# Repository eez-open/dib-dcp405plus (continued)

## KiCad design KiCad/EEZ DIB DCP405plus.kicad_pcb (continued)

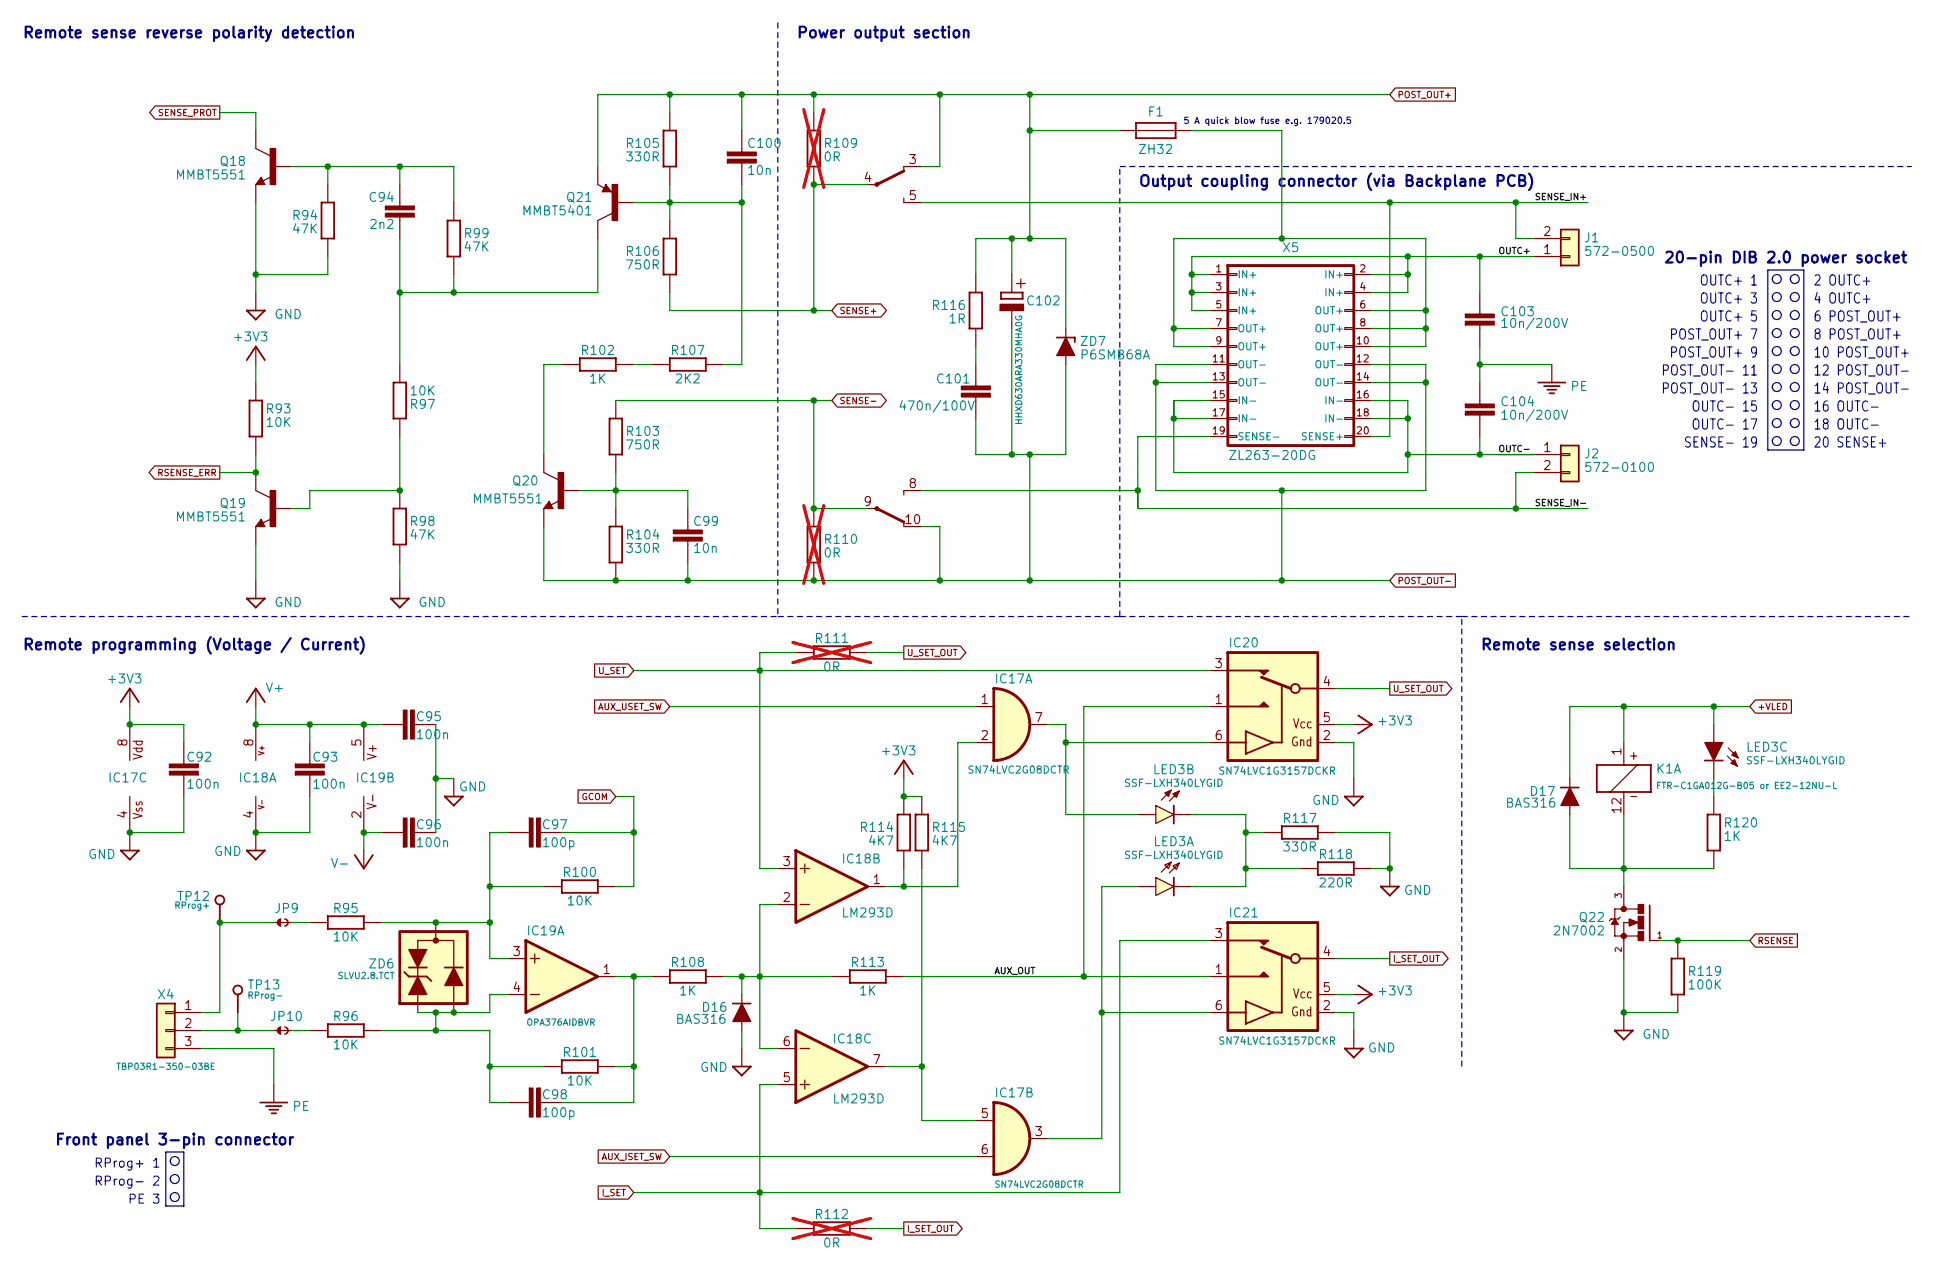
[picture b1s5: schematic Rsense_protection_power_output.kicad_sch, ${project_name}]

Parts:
C92, C93, C95, C96: 100n; C_0603_1608Metric; DigiKey 1276-6717-1-ND
C94: 2n2; C_0805_2012Metric; DigiKey 1276-2478-1-ND
C97, C98: 100p; C_0805_2012Metric; DigiKey 399-15000-1-ND
C99, C100: 10n; C_0805_2012Metric; DigiKey 490-7194-1-ND
C101: 470n/100V; C_0805_2012Metric; DigiKey 587-5014-1-ND
C102: HHXD630ARA330MHA0G; CAPAE830X1050N; DigiKey 565-HHXD630ARA330MHA0GCT-ND
C103, C104: 10n/200V; C_1206_3216Metric; DigiKey 311-4491-1-ND
D16, D17: BAS316; SOD-323_1P8X1P35_ONS-M; DigiKey 5399-BAS316CT-ND
F1: ZH32; DigiKey 732-11370-ND
IC17: SN74LVC2G08DCTR; DCT8; DigiKey 1727-5987-1-ND
IC18: LM293D; SOIC127P600X173-8N; DigiKey LM293DR2GOSCT-ND
IC19: OPA376AIDBVR; SOT23-5L_STM; DigiKey 296-39130-1-ND
IC20, IC21: SN74LVC1G3157DCKR; SOT65P210X110-6N; DigiKey 296-14909-1-ND
J1: 572-0500; Mouser 164-6221
J2: 572-0100; Mouser 164-6220
JP9, JP10: JP2-NOCUT-0805; JP2 shorted (0603)
K1: FTR-C1GA012G-B05 or EE2-12NU-L; FTR-C1; DigiKey 399-10997-1-ND
LED3: SSF-LXH340LYGID; DigiKey SSF-LXH340LYGID-ND
Q18, Q19, Q20: MMBT5551; SOT23-BEC; DigiKey MMBT5551LT1GOSCT-ND
Q21: MMBT5401; SOT23-BEC; DigiKey MMBT5401-FDICT-ND
Q22: 2N7002; SOT103P240X110-3N; DigiKey T2N7002AKLMCT-ND
R93, R95, R96, R97, R100, R101: 10K; R_0805_2012Metric; DigiKey 311-10.0KCRCT-ND
R94, R98, R99: 47K; R_0805_2012Metric; DigiKey RHM47KKCT-ND
R102, R108, R113, R120: 1K; R_0805_2012Metric; DigiKey 311-1.00KCRCT-ND
R103, R106: 750R; R_0805_2012Metric; DigiKey A126385CT-ND
R104, R105, R117: 330R; R_0805_2012Metric; DigiKey A129743CT-ND
R107: 2K2; R_0805_2012Metric; DigiKey 311-2.20KCRCT-ND
R109, R110, R111, R112: 0R; R_0603_1608Metric; not fitted
R114, R115: 4K7; R_0805_2012Metric; DigiKey 311-4.70KCRCT-ND
R116: 1R; R_0805_2012Metric; DigiKey 13-RC0805FR-131RLCT-ND
R118: 220R; R_0805_2012Metric; DigiKey RMCF0805FT220RCT-ND
R119: 100K; R_0805_2012Metric; DigiKey RMCF0805FT100KCT-ND
TP12, TP13: PCB_TEST_TABSHIELD; Testhole 24_50mils
X4: TBP03R1-350-03BE; DigiKey 2223-TBP03R1-350-03BE-ND
X5: ZL263-20DG; SSW-110-02-T-D-RA; DigiKey PPPC102LJBN-RC
ZD6: SLVU2.8.TCT; SOT23-3; DigiKey SLVU2.8.TCTCT-ND
ZD7: P6SMB68A; DO214AA; DigiKey P6SMB68ABBCT-ND

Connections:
+3V3: C92.2, IC17.8 (VDD), IC20.5 (VDD), IC21.5 (VDD), R93.2, R114.1, R115.1; also elsewhere on the board
+VLED: D17.C, K1.1 (C1), LED3.YA; also elsewhere on the board
/Rsense protection, power output, Rprog/AUX_OUT: IC20.1 (NO), IC21.1 (NO), R113.1
/Rsense protection, power output, Rprog/OUTC+: C103.1, J1.1, X5.1 (IN+), X5.2 (IN+), X5.3 (IN+), X5.4 (IN+), X5.5 (IN+)
/Rsense protection, power output, Rprog/OUTC-: C104.2, J2.1, X5.15 (IN-), X5.16 (IN-), X5.17 (IN-), X5.18 (IN-)
/Rsense protection, power output, Rprog/SENSE_IN+: J1.2, K1.5 (NO), X5.20 (SENSE+)
/Rsense protection, power output, Rprog/SENSE_IN-: J2.2, K1.8 (NO), X5.19 (SENSE-)
AUX_ISET_SW: IC17.6 (I1); also elsewhere on the board
AUX_USET_SW: IC17.1 (I0); also elsewhere on the board
GCOM: C97.1, R100.1; also elsewhere on the board
GND: C92.1, C93.2, C95.2, C96.2, D16.A, IC17.4 (VSS), IC18.4 (V-), IC20.2 (GND), IC21.2 (GND), Q18.E, Q19.E, Q22.2 (S), R94.1, R98.1, R117.1, R118.1, R119.1; also elsewhere on the board
I_SET: IC18.5 (+IN), IC21.3 (NC), R112.2; also elsewhere on the board
I_SET_OUT: IC21.4 (COM), R112.1; also elsewhere on the board
unnamed: C94.1, Q18.B, R94.2, R99.2
unnamed: C94.2, Q21.C, R97.2, R99.1
unnamed: C99.1, Q20.B, R103.1, R104.2
unnamed: C100.2, Q21.B, R105.1, R106.2, R107.2
unnamed: C101.2, R116.2
unnamed: F1.2, X5.6 (OUT+), X5.7 (OUT+), X5.8 (OUT+), X5.9 (OUT+), X5.10 (OUT+)
unnamed: IC17.2 (I1), IC18.1 (OUT), R114.2
unnamed: IC17.7 (O), IC20.6 (CTRL), LED3.GA
unnamed: IC17.5 (I0), IC18.7 (OUT), R115.2
unnamed: IC17.3 (O), IC21.6 (CTRL), LED3.RA
unnamed: D16.C, IC18.2 (-IN), IC18.6 (-IN), R108.1, R113.2
unnamed: C97.2, IC19.3 (+IN), R95.1, R100.2, ZD6.3
unnamed: C98.2, IC19.4 (-IN), R96.1, R101.2, ZD6.1, ZD6.2
unnamed: C98.1, IC19.1 (OUT), R101.1, R108.2
unnamed: JP9.2, R95.2
unnamed: JP10.2, R96.2
unnamed: D17.A, K1.12 (C2), Q22.3 (D), R120.1
unnamed: LED3.GC, LED3.RC, R117.2, R118.2
unnamed: LED3.YC, R120.2
unnamed: Q19.B, R97.1, R98.2
unnamed: Q20.C, R102.1
unnamed: R102.2, R107.1
unnamed: JP9.1, TP12.1 (P$1_1), X4.1
unnamed: JP10.1, TP13.1 (P$1_1), X4.2
PE: C103.2, C104.1, X4.3; also elsewhere on the board
POST_OUT+: C100.1, C102.+, F1.1, K1.3 (NC), Q21.E, R105.2, R109.1, R116.1, ZD7.C; also elsewhere on the board
POST_OUT-: C99.2, C101.1, C102.-, K1.10 (NC), Q20.E, R104.1, R110.2, X5.11 (OUT-), X5.12 (OUT-), X5.13 (OUT-), X5.14 (OUT-), ZD7.A; also elsewhere on the board
RSENSE: Q22.1 (G), R119.2; also elsewhere on the board
RSENSE_ERR: Q19.C, R93.1; also elsewhere on the board
SENSE+: K1.4 (COM), R106.1, R109.2; also elsewhere on the board
SENSE-: K1.9 (COM), R103.2, R110.1; also elsewhere on the board
SENSE_PROT: Q18.C; also elsewhere on the board
U_SET: IC18.3 (+IN), IC20.3 (NC), R111.2; also elsewhere on the board
U_SET_OUT: IC20.4 (COM), R111.1; also elsewhere on the board
V+: C93.1, C95.1, IC18.8 (V+), IC19.5 (V+); also elsewhere on the board
V-: C96.1, IC19.2 (V-); also elsewhere on the board

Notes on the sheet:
8 POST_OUT+
PE 3
16 OUTC-
POST_OUT- 11
12 POST_OUT-
Remote sense reverse polarity detection
POST_OUT+ 9
OUTC- 17
Output coupling connector (via Backplane PCB)
POST_OUT- 13
Remote programming (Voltage / Current)
10 POST_OUT+
4 OUTC+
6 POST_OUT+
2 OUTC+
OUTC+ 5
14 POST_OUT-
18 OUTC-
POST_OUT+ 7
OUTC+ 1
RProg+ 1
20 SENSE+
Front panel 3-pin connector
OUTC+ 3
5 A quick blow fuse e.g. 179020.5
RProg- 2
Power output section
Remote sense selection
SENSE- 19
OUTC- 15
20-pin DIB 2.0 power socket

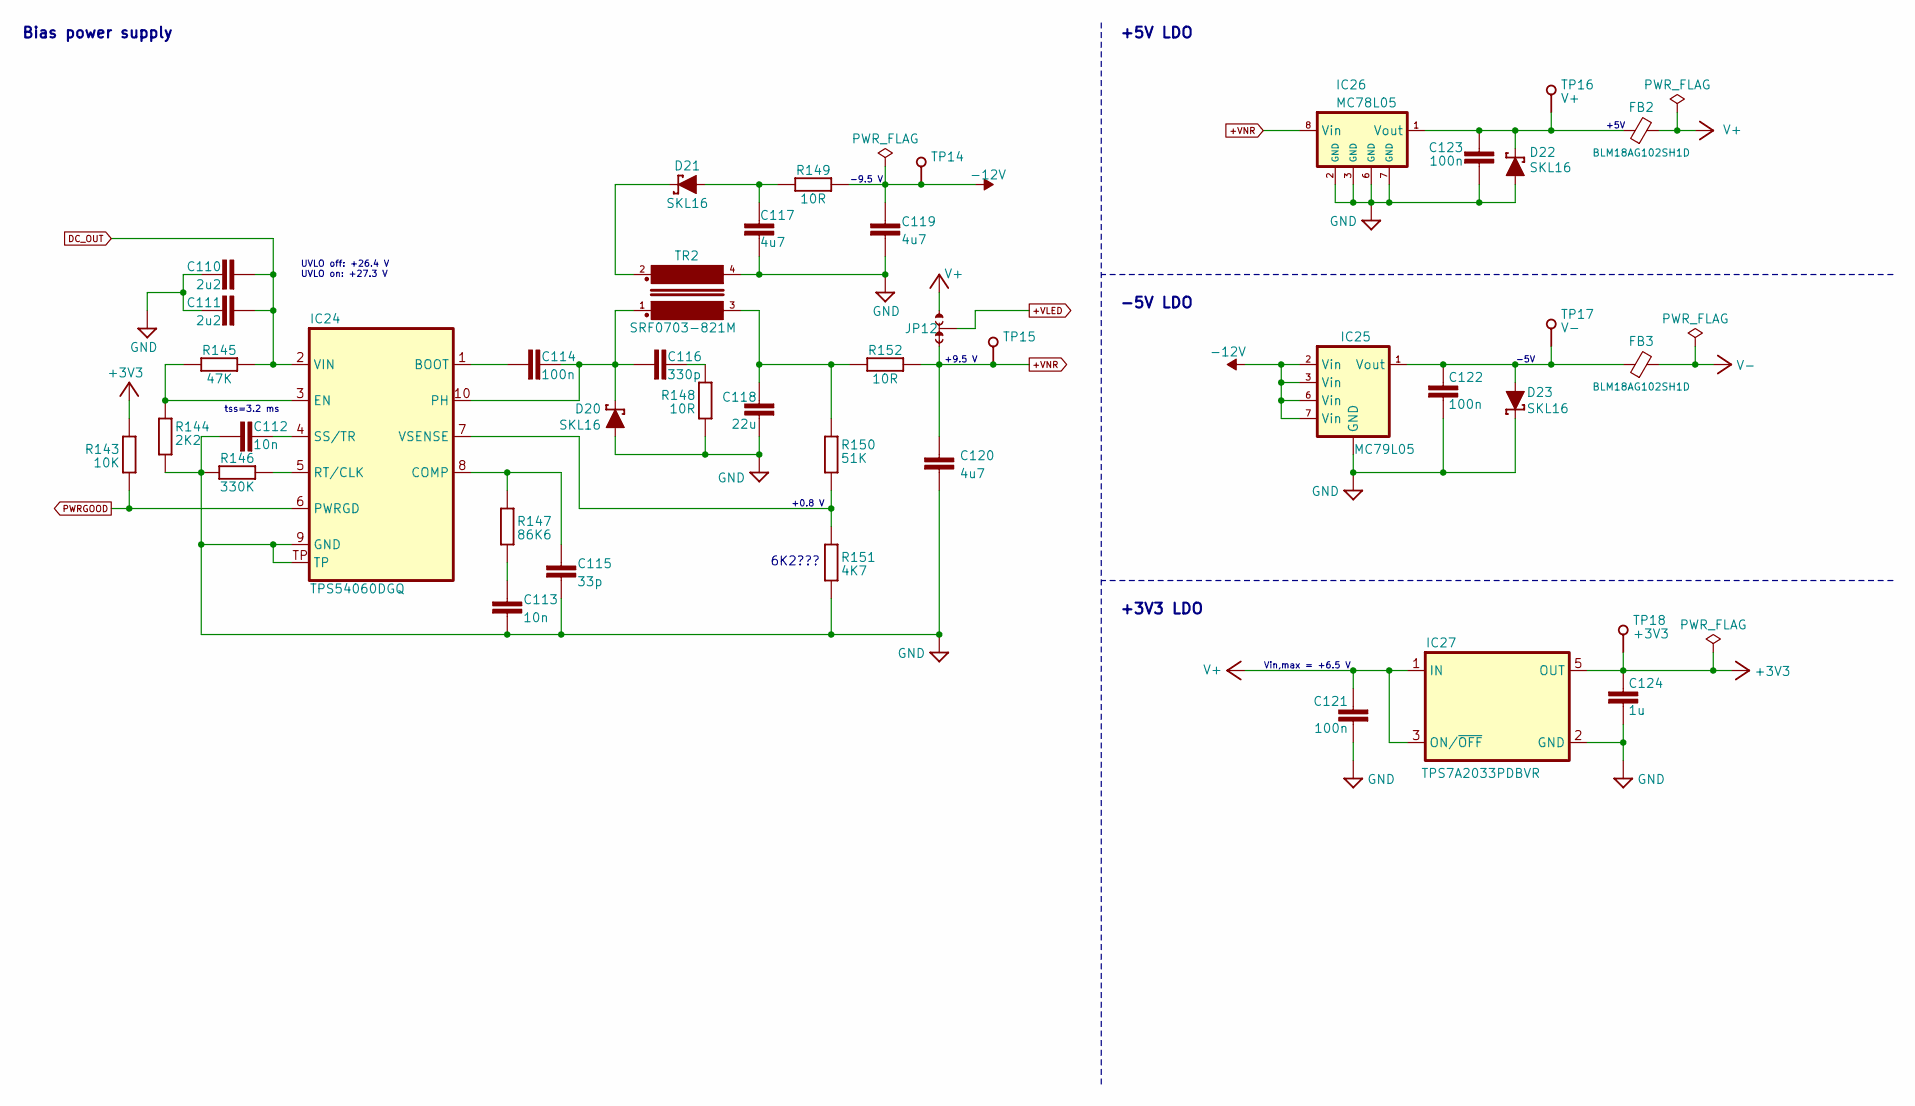
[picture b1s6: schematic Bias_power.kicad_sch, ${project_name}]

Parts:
C110, C111: 2u2; C_1206_3216Metric; DigiKey 1276-3138-1-ND
C112, C113: 10n; C_0805_2012Metric; DigiKey 490-7194-1-ND
C114, C121, C122, C123: 100n; C_0603_1608Metric; DigiKey 1276-6717-1-ND
C115: 33p; C_0805_2012Metric; DigiKey 399-C0805C330J5GACTUCT-ND
C116: 330p; C_0805_2012Metric; DigiKey 311-1117-1-ND
C117, C119, C120: 4u7; C_0805_2012Metric; DigiKey 1276-CL21A475KACLRNCCT-ND
C118: 22u; C_1210_3225Metric; DigiKey 1276-1851-1-ND
C124: 1u; C_0805_2012Metric; DigiKey 1276-2931-1-ND
D20, D21, D22, D23: SKL16; SOD123; DigiKey RB160MM-60CT-ND
FB2, FB3: BLM18AG102SH1D; BEAD0603; DigiKey 490-7809-1-ND
IC24: TPS54060DGQ; SOP50P490X110-11N; DigiKey 296-37148-1-ND
IC25: MC79L05; SOIC127P600X173-8N; DigiKey MC79L05ACDR2GOSCT-ND
IC26: MC78L05; SOIC127P600X173-8N; DigiKey MC78L05ACDR2GOSCT-ND
IC27: TPS7A2033PDBVR; SOT23-5L_STM; DigiKey 296-TPS7A2033PDBVRCT-ND
JP12: JP3 shorted (0603)
R143: 10K; R_0805_2012Metric; DigiKey 311-10.0KCRCT-ND
R144: 2K2; R_0805_2012Metric; DigiKey 311-2.20KCRCT-ND
R145: 47K; R_0805_2012Metric; DigiKey RHM47KKCT-ND
R146: 330K; R_0805_2012Metric; DigiKey A126361CT-ND
R147: 86K6; R_0805_2012Metric; DigiKey 311-86.6KCRCT-ND
R148, R149, R152: 10R; R_0805_2012Metric; DigiKey 311-10.0CRCT-ND
R150: 51K; R_0805_2012Metric; DigiKey 311-51.0KCRCT-ND
R151: 4K7; R_0805_2012Metric; DigiKey 311-4.70KCRCT-ND
TP14, TP15, TP16, TP17, TP18: TEST-PIN_0.9MM; Testhole 24_50mils
TR2: SRF0703-821M; SRF0703; DigiKey SRF0703-821MCT-ND

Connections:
+3V3: C124.2, IC27.5 (OUT), R143.1, TP18.1 (P$1_1); also elsewhere on the board
+VLED: JP12.COM; also elsewhere on the board
+VNR: C120.1, IC26.8 (Vin), JP12.NC, R152.2, TP15.1 (P$1_1); also elsewhere on the board
-12V: C119.1, IC25.2 (Vin), IC25.3 (Vin), IC25.6 (Vin), IC25.7 (Vin), R149.2, TP14.1 (P$1_1); also elsewhere on the board
DC_OUT: C110.1, C111.1, IC24.2 (VIN), R145.2; also elsewhere on the board
GND: C110.2, C111.2, C112.2, C113.1, C115.1, C117.2, C118.2, C119.2, C120.2, C121.1, C122.1, C123.2, C124.1, D20.A, D22.A, D23.C, IC24.9 (GND), IC24.TP, IC25.5 (GND), IC26.2 (GND), IC26.3 (GND), IC26.6 (GND), IC26.7 (GND), IC27.2 (GND), R144.1, R146.1, R148.2, R151.2, TR2.4; also elsewhere on the board
unnamed: C113.2, R147.1
unnamed: C116.2, R148.1
unnamed: C117.1, D21.A, R149.1
unnamed: C118.1, R150.1, R152.1, TR2.3
unnamed: D21.C, TR2.2
unnamed: C114.2, IC24.1 (BOOT)
unnamed: C115.2, IC24.8 (COMP), R147.2
unnamed: IC24.3 (EN), R144.2, R145.1
unnamed: C114.1, C116.1, D20.C, IC24.10 (PH), TR2.1
unnamed: IC24.5 (RT/CLK), R146.2
unnamed: C112.1, IC24.4 (SS/TR)
unnamed: IC24.7 (VSENSE), R150.2, R151.1
unnamed: C122.2, D23.A, FB3.1, IC25.1 (Vout), TP17.1 (P$1_1)
unnamed: C123.1, D22.C, FB2.1, IC26.1 (Vout), TP16.1 (P$1_1)
PWRGOOD: IC24.6 (PWRGD), R143.2; also elsewhere on the board
V+: C121.2, FB2.2, IC27.1 (IN), IC27.3 (ON/~OFF), JP12.NO; also elsewhere on the board
V-: FB3.2; also elsewhere on the board

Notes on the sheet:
+5V
UVLO off: +26.4 V UVLO on: +27.3 V
Vin,max = +6.5 V
+5V LDO
Bias power supply
-5V LDO
+0.8 V
+3V3 LDO
6K2???
-5V
-9.5 V
tss=3.2 ms
+9.5 V

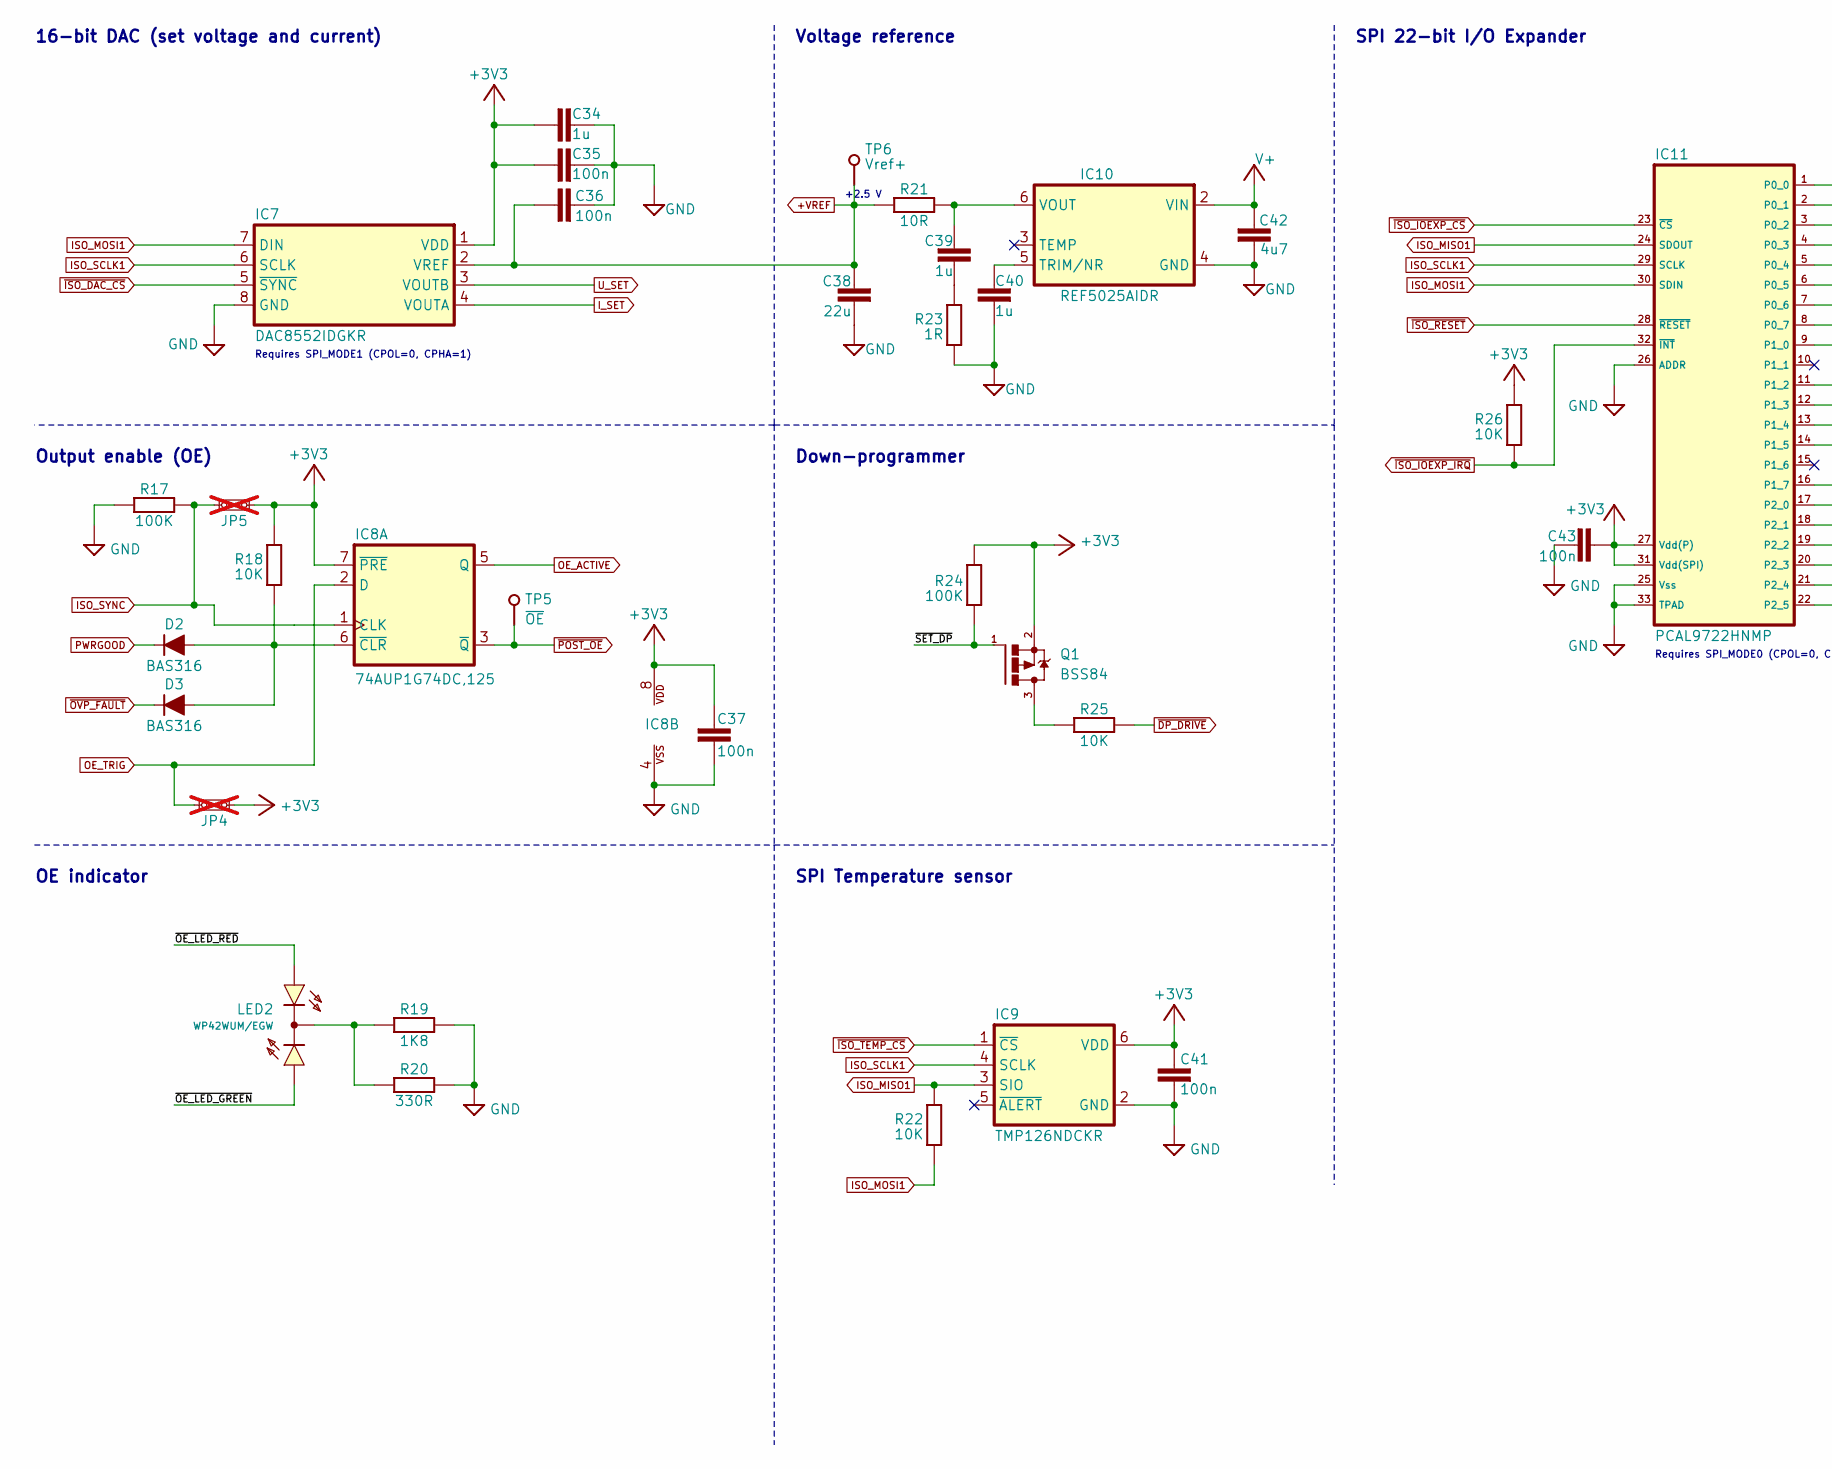
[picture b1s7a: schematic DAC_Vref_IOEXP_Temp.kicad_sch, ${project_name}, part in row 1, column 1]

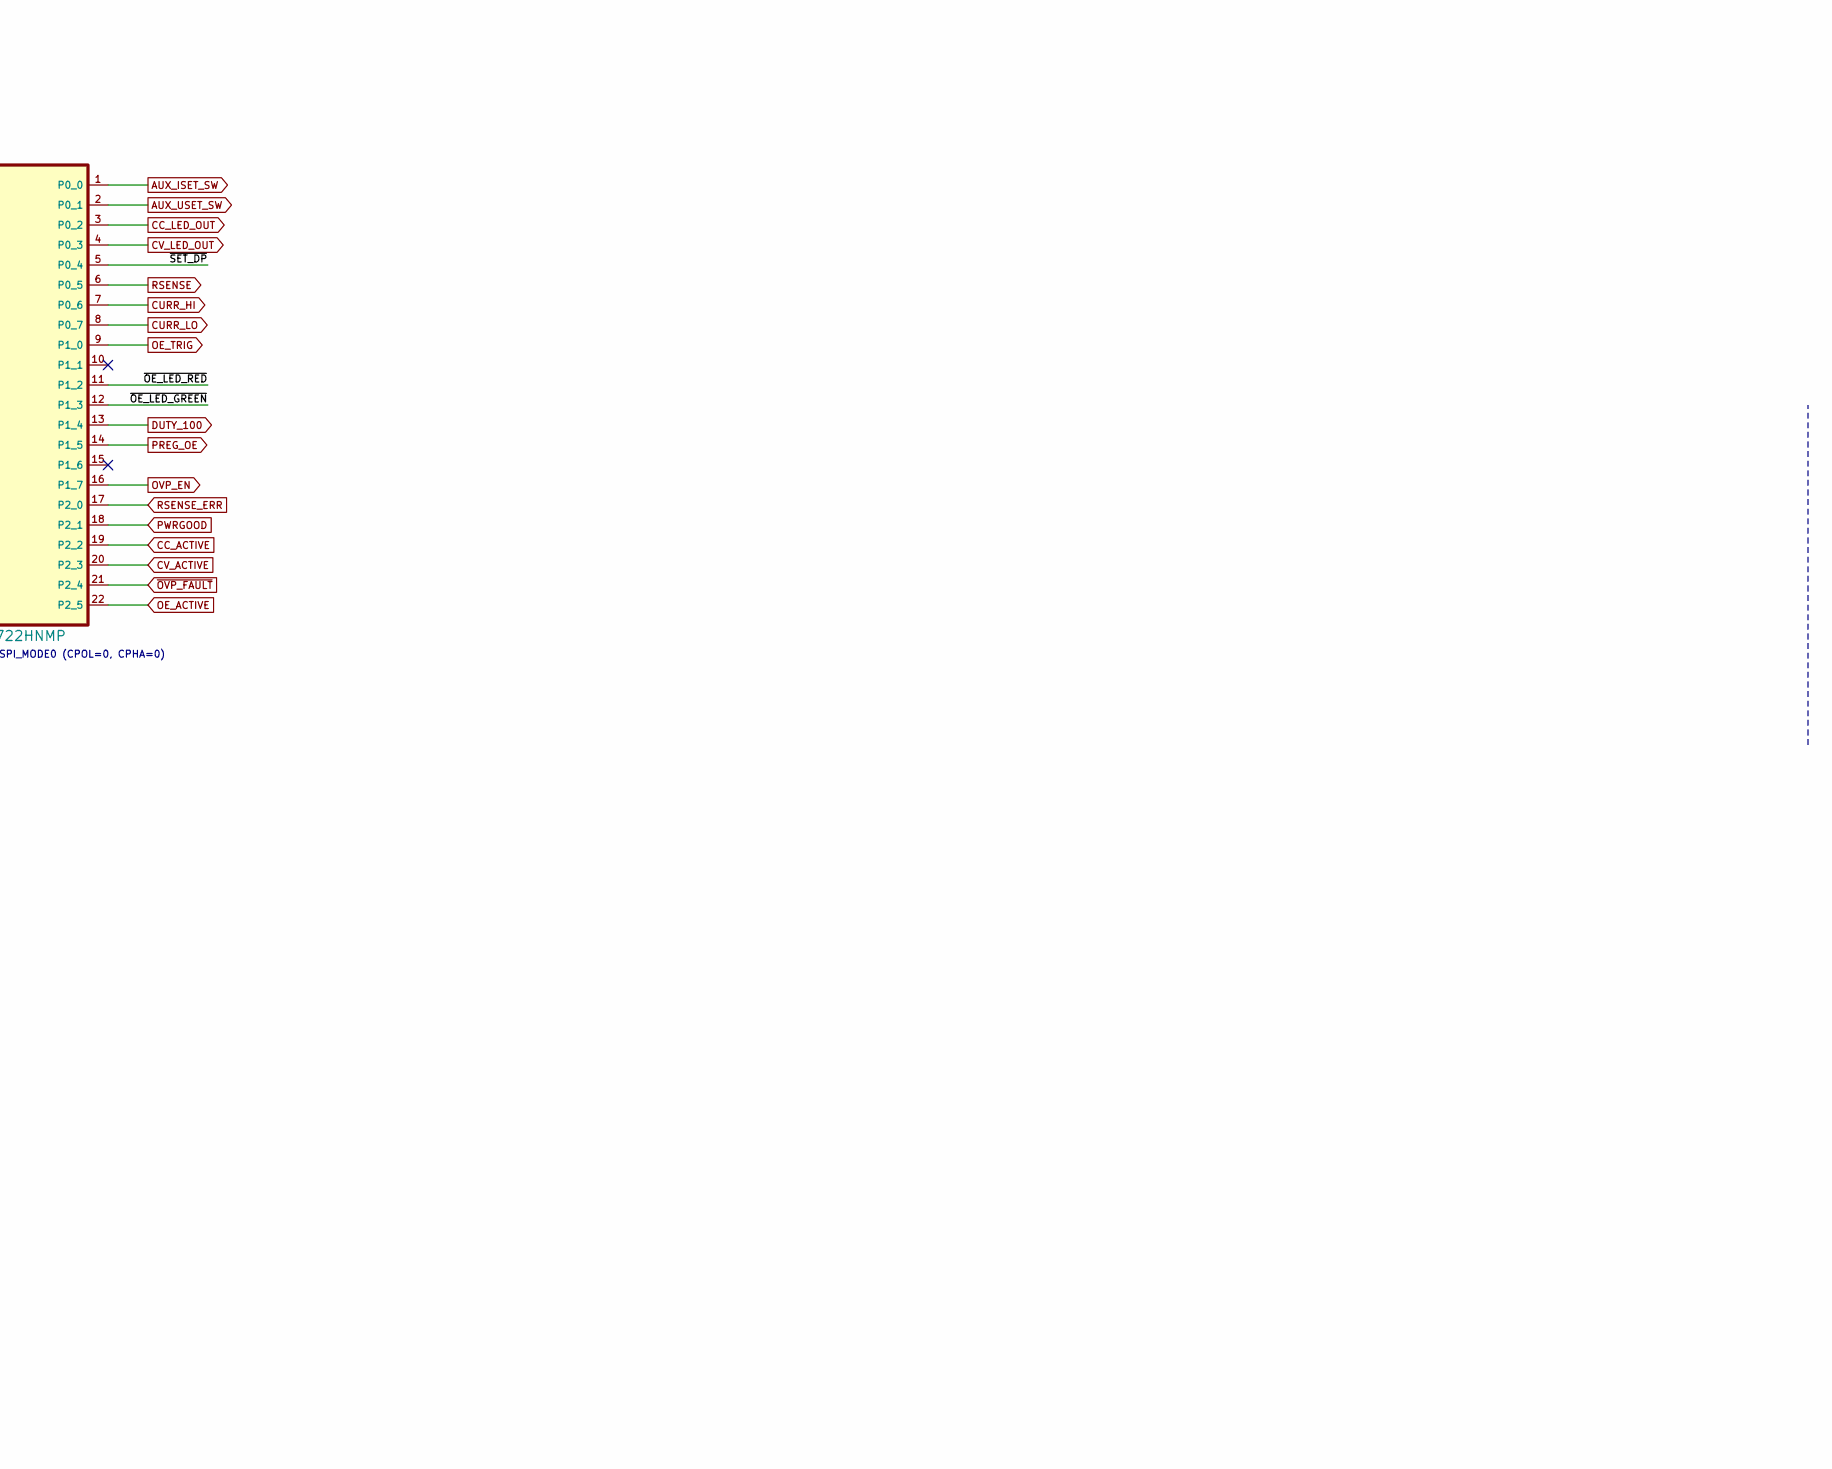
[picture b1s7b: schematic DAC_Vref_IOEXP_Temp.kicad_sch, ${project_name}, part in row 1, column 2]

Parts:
C34, C39, C40: 1u; C_0805_2012Metric; DigiKey 1276-2931-1-ND
C35, C36, C37, C41, C43: 100n; C_0603_1608Metric; DigiKey 1276-6717-1-ND
C38: 22u; C_1210_3225Metric; DigiKey 1276-1851-1-ND
C42: 4u7; C_0805_2012Metric; DigiKey 1276-CL21A475KACLRNCCT-ND
D2, D3: BAS316; SOD-323_1P8X1P35_ONS-M; DigiKey 5399-BAS316CT-ND
IC7: DAC8552IDGKR; DGK8-M; DigiKey 296-46082-1-ND
IC8: 74AUP1G74DC,125; DCU8; DigiKey 1727-74AUP1G74DC-Q100HCT-ND
IC9: TMP126NDCKR; DCK6; DigiKey 296-TMP126NDCKRCT-ND
IC10: REF5025AIDR; SOIC127P600X173-8N; DigiKey 296-41382-1-ND
IC11: PCAL9722HNMP; HVQFN32_SOT617-1_NXP-M; DigiKey 568-PCAL9722HNMPCT-ND
JP4, JP5: M22-2010246; DigiKey M22-2010346-ND; not fitted
LED2: WP42WUM/EGW; L-42WUM-1EGWT; DigiKey 754-1718-ND
Q1: BSS84; SOT103P240X110-3N; DigiKey BSS84LT1GOSCT-ND
R17, R24: 100K; R_0805_2012Metric; DigiKey RMCF0805FT100KCT-ND
R18, R22, R25, R26: 10K; R_0805_2012Metric; DigiKey 311-10.0KCRCT-ND
R19: 1K8; R_0805_2012Metric; DigiKey 311-1.80KCRCT-ND
R20: 330R; R_0805_2012Metric; DigiKey A129743CT-ND
R21: 10R; R_0805_2012Metric; DigiKey 311-10.0CRCT-ND
R23: 1R; R_0805_2012Metric; DigiKey 13-RC0805FR-131RLCT-ND
TP5: TEST-PIN_0.9MM; Testhole 24_50mils
TP6: PCB_TEST_TABSHIELD; Testhole 24_50mils

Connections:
+3V3: C34.1, C35.2, C37.2, C41.1, C43.2, IC7.1 (VDD), IC8.7 (~PRE), IC8.8 (VDD), IC9.6 (VDD), IC11.27 (Vdd(P)), IC11.31 (Vdd(SPI)), JP4.1, JP5.1, Q1.2 (S), R18.2, R24.1, R26.2; also elsewhere on the board
+VREF: C36.2, C38.1, IC7.2 (VREF), R21.1, TP6.1 (P$1_1); also elsewhere on the board
/DAC, OE, Vref, IOEXP, Temp/~OE_LED_GREEN: IC11.12 (P1_3), LED2.GREEN (AG)
/DAC, OE, Vref, IOEXP, Temp/~OE_LED_RED: IC11.11 (P1_2), LED2.RED (AR)
/DAC, OE, Vref, IOEXP, Temp/~SET_DP: IC11.5 (P0_4), Q1.1 (G), R24.2
AUX_ISET_SW: IC11.1 (P0_0); also elsewhere on the board
AUX_USET_SW: IC11.2 (P0_1); also elsewhere on the board
CC_ACTIVE: IC11.19 (P2_2); also elsewhere on the board
CC_LED_OUT: IC11.3 (P0_2); also elsewhere on the board
CURR_HI: IC11.7 (P0_6); also elsewhere on the board
CURR_LO: IC11.8 (P0_7); also elsewhere on the board
CV_ACTIVE: IC11.20 (P2_3); also elsewhere on the board
CV_LED_OUT: IC11.4 (P0_3); also elsewhere on the board
DUTY_100: IC11.13 (P1_4); also elsewhere on the board
GND: C34.2, C35.1, C36.1, C37.1, C38.2, C40.2, C41.2, C42.2, C43.1, IC7.8 (GND), IC8.4 (VSS), IC9.2 (GND), IC10.4 (GND), IC11.25 (Vss), IC11.26 (ADDR), IC11.33 (TPAD), R17.1, R19.2, R20.2, R23.2; also elsewhere on the board
ISO_MISO1: IC9.3 (SIO), IC11.24 (SDOUT), R22.2; also elsewhere on the board
ISO_MOSI1: IC7.7 (DIN), IC11.30 (SDIN), R22.1; also elsewhere on the board
ISO_SCLK1: IC7.6 (SCLK), IC9.4 (SCLK), IC11.29 (SCLK); also elsewhere on the board
ISO_SYNC: IC8.1 (CLK), JP5.2, R17.2; also elsewhere on the board
I_SET: IC7.4 (VOUTA); also elsewhere on the board
unnamed: C39.2, R23.1
unnamed: D2.A, D3.A, IC8.6 (~CLR), R18.1
unnamed: C40.1, IC10.5 (TRIM/NR)
unnamed: C39.1, IC10.6 (VOUT), R21.2
unnamed: LED2.CC (C), R19.1, R20.1
unnamed: Q1.3 (D), R25.2
OE_ACTIVE: IC8.5 (Q), IC11.22 (P2_5)
OE_TRIG: IC8.2 (D), IC11.9 (P1_0), JP4.2
OVP_EN: IC11.16 (P1_7); also elsewhere on the board
PREG_OE: IC11.14 (P1_5); also elsewhere on the board
PWRGOOD: D2.C, IC11.18 (P2_1); also elsewhere on the board
RSENSE: IC11.6 (P0_5); also elsewhere on the board
RSENSE_ERR: IC11.17 (P2_0); also elsewhere on the board
U_SET: IC7.3 (VOUTB); also elsewhere on the board
V+: C42.1, IC10.2 (VIN); also elsewhere on the board
~DP_DRIVE: R25.1; also elsewhere on the board
~ISO_DAC_CS: IC7.5 (~SYNC); also elsewhere on the board
~ISO_IOEXP_CS: IC11.23 (~CS); also elsewhere on the board
~ISO_IOEXP_IRQ: IC11.32 (~INT), R26.1; also elsewhere on the board
~ISO_RESET: IC11.28 (~RESET); also elsewhere on the board
~ISO_TEMP_CS: IC9.1 (~CS); also elsewhere on the board
~OVP_FAULT: D3.C, IC11.21 (P2_4); also elsewhere on the board
~POST_OE: IC8.3 (~Q), TP5.1 (P$1_1); also elsewhere on the board

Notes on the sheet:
Voltage reference
Requires SPI_MODE0 (CPOL=0, CPHA=0)
Down-programmer
Requires SPI_MODE1 (CPOL=0, CPHA=1)
Output enable (OE)
16-bit DAC (set voltage and current)
+2.5 V
SPI Temperature sensor
OE indicator
SPI 22-bit I/O Expander
